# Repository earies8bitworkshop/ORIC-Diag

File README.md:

# ORIC-Diag
This is a convertion of the ORIC Diagnostic PCB located at https://oric.signal11.org.uk/html/diagrom.htm Unfortunately with EAGLE going end of life it was tough going to get the PCB orders. This is a KICAD conversion of the original, no changes made as of 7/9/25. The Gerbers are located in production/OricDiagBoard.zip and can be uploaded directly to your favourite PCB manufacturer. 

NOTE: Mike Brown is the original author of the works, I take no credit for it this is a direct conversion into Kicad only.

NOTE: The kicad coversion needs some clean up it misidentified the diodes as Pots. If you make changes to the board feel free to tidy up the autoconversion but what we have is good enough to generate the gerbers for manufacture.

# Oric Repair Checklist
Again, just a conversion. This time adding the PCB images into the word doc rather than being in a separate ZIP file. All credits go to the Author MJB. Also corrected the text with the errata noted on the source web site. https://oric.signal11.org.uk/html/repairguide.htm

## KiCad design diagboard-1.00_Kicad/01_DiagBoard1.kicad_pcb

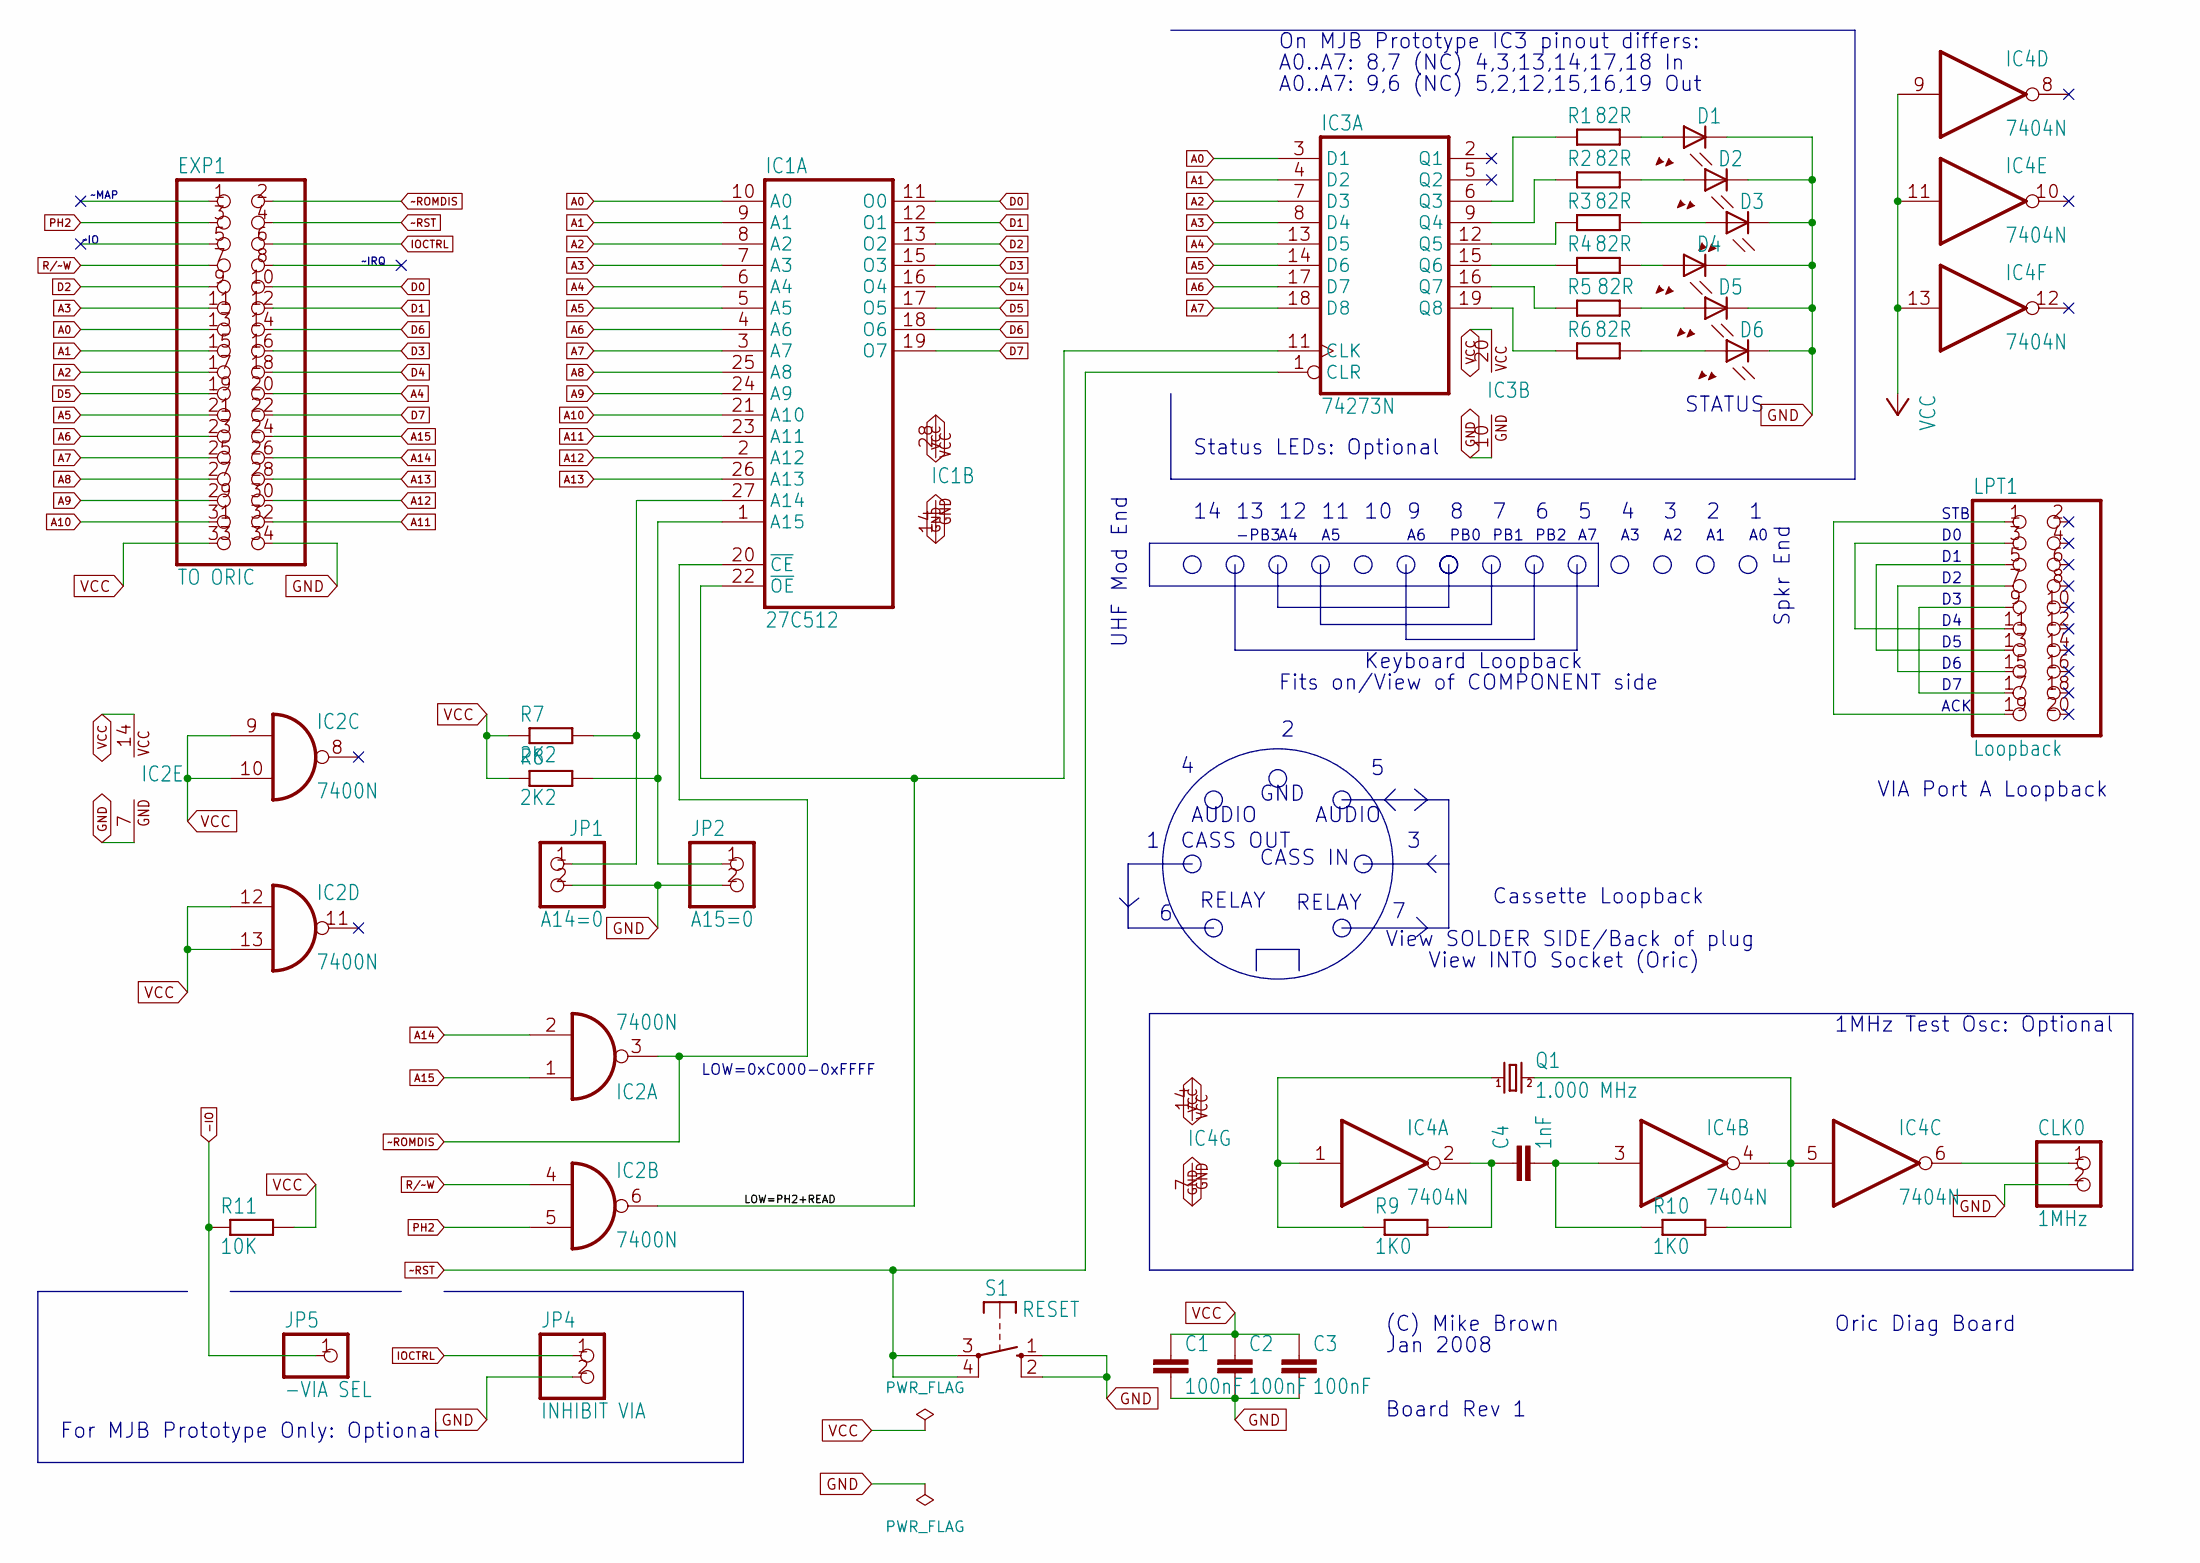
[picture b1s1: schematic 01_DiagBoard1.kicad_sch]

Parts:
C1, C2, C3: 100nF; C050-024X044
C4: 1nF; C050-024X044
CLK0: 1MHz; 1X02
D1, D2, D3, D4, D5, D6: U57X32
EXP1: TO ORIC; 2X17
IC1: 27C512; DIL28
IC2: 7400N; DIL14
IC3: 74273N; DIL20
IC4: 7404N; DIL14
JP1: A14=0; 1X02
JP2: A15=0; 1X02
JP4: INHIBIT VIA; 1X02
JP5: -VIA SEL; 1X01
LPT1: Loopback; 2X10
Q1: 1.000 MHz; HC18U-V
R1, R2, R3, R4, R5, R6: 82R; 0204V
R7, R8: 2K2; 0204V
R9, R10: 1K0; 0204V
R11: 10K; 0204V
S1: RESET; DT6

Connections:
-IO: JP5.1, R11.1
/LOW=PH2+READ: IC1.22 (~OE), IC2.6 (O), IC3.11 (CLK)
A0: EXP1.13, IC1.10 (A0), IC3.3 (D1)
A1: EXP1.15, IC1.9 (A1), IC3.4 (D2)
A2: EXP1.17, IC1.8 (A2), IC3.7 (D3)
A3: EXP1.11, IC1.7 (A3), IC3.8 (D4)
A4: EXP1.20, IC1.6 (A4), IC3.13 (D5)
A5: EXP1.21, IC1.5 (A5), IC3.14 (D6)
A6: EXP1.23, IC1.4 (A6), IC3.17 (D7)
A7: EXP1.25, IC1.3 (A7), IC3.18 (D8)
A8: EXP1.27, IC1.25 (A8)
A9: EXP1.29, IC1.24 (A9)
A10: EXP1.31, IC1.21 (A10)
A11: EXP1.32, IC1.23 (A11)
A12: EXP1.30, IC1.2 (A12)
A13: EXP1.28, IC1.26 (A13)
A14: EXP1.26, IC2.2 (I1)
A15: EXP1.24, IC2.1 (I0)
D0: EXP1.10, IC1.11 (O0)
D1: EXP1.12, IC1.12 (O1)
D2: EXP1.9, IC1.13 (O2)
D3: EXP1.16, IC1.15 (O3)
D4: EXP1.18, IC1.16 (O4)
D5: EXP1.19, IC1.17 (O5)
D6: EXP1.14, IC1.18 (O6)
D7: EXP1.22, IC1.19 (O7)
GND: C1.2, C2.2, C3.2, CLK0.2, D1.K (C), D2.K (C), D3.K (C), D4.K (C), D5.K (C), D6.K (C), EXP1.34, IC1.14 (GND), IC2.7 (GND), IC3.10 (GND), IC4.7 (GND), JP1.2, JP2.2, JP4.2, S1.1 (S), S1.2 (S@1)
IOCTRL: EXP1.6, JP4.1
unnamed: D1.A, R1.2
unnamed: D2.A, R2.2
unnamed: D3.A, R3.2
unnamed: D4.A, R4.2
unnamed: D5.A, R5.2
unnamed: D6.A, R6.2
unnamed: IC1.27 (A14), JP1.1, R7.2
unnamed: IC1.1 (A15), JP2.1, R8.2
unnamed: IC3.6 (Q3), R1.1
unnamed: IC3.9 (Q4), R2.1
unnamed: IC3.12 (Q5), R3.1
unnamed: IC3.15 (Q6), R4.1
unnamed: IC3.16 (Q7), R5.1
unnamed: IC3.19 (Q8), R6.1
unnamed: IC4.1 (I), Q1.1, R9.1
unnamed: C4.1, IC4.2 (O), R9.2
unnamed: C4.2, IC4.3 (I), R10.1
unnamed: IC4.4 (O), IC4.5 (I), Q1.2, R10.2
unnamed: CLK0.1, IC4.6 (O)
unnamed: LPT1.1, LPT1.19
unnamed: LPT1.3, LPT1.11
unnamed: LPT1.5, LPT1.13
unnamed: LPT1.7, LPT1.15
unnamed: LPT1.9, LPT1.17
PH2: EXP1.3, IC2.5 (I1)
R/~W: EXP1.7, IC2.4 (I0)
VCC: C1.1, C2.1, C3.1, EXP1.33, IC1.28 (VCC), IC2.9 (I0), IC2.10 (I1), IC2.12 (I0), IC2.13 (I1), IC2.14 (VCC), IC3.20 (VCC), IC4.9 (I), IC4.11 (I), IC4.13 (I), IC4.14 (VCC), R7.1, R8.1, R11.2
~ROMDIS: EXP1.2, IC1.20 (~CE), IC2.3 (O)
~RST: EXP1.4, IC3.1 (CLR), S1.3, S1.4 (P@1)

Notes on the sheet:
~IRQ
Status LEDs: Optional
AUDIO
UHF Mod End
On MJB Prototype IC3 pinout differs:
~IO
PB1
ACK
PB2
1MHz Test Osc: Optional
CASS OUT
STB
Spkr End
Oric Diag Board
Cassette Loopback
Board Rev 1
For MJB Prototype Only: Optional
-PB3
~MAP
PB0
Fits on/View of COMPONENT side
Jan 2008
A0..A7: 8,7 (NC) 4,3,13,14,17,18 In
RELAY
VIA Port A Loopback
A0..A7: 9,6 (NC) 5,2,12,15,16,19 Out
Keyboard Loopback
View INTO Socket (Oric)
CASS IN
GND
View SOLDER SIDE/Back of plug
LOW=0xC000-0xFFFF
(C) Mike Brown
STATUS

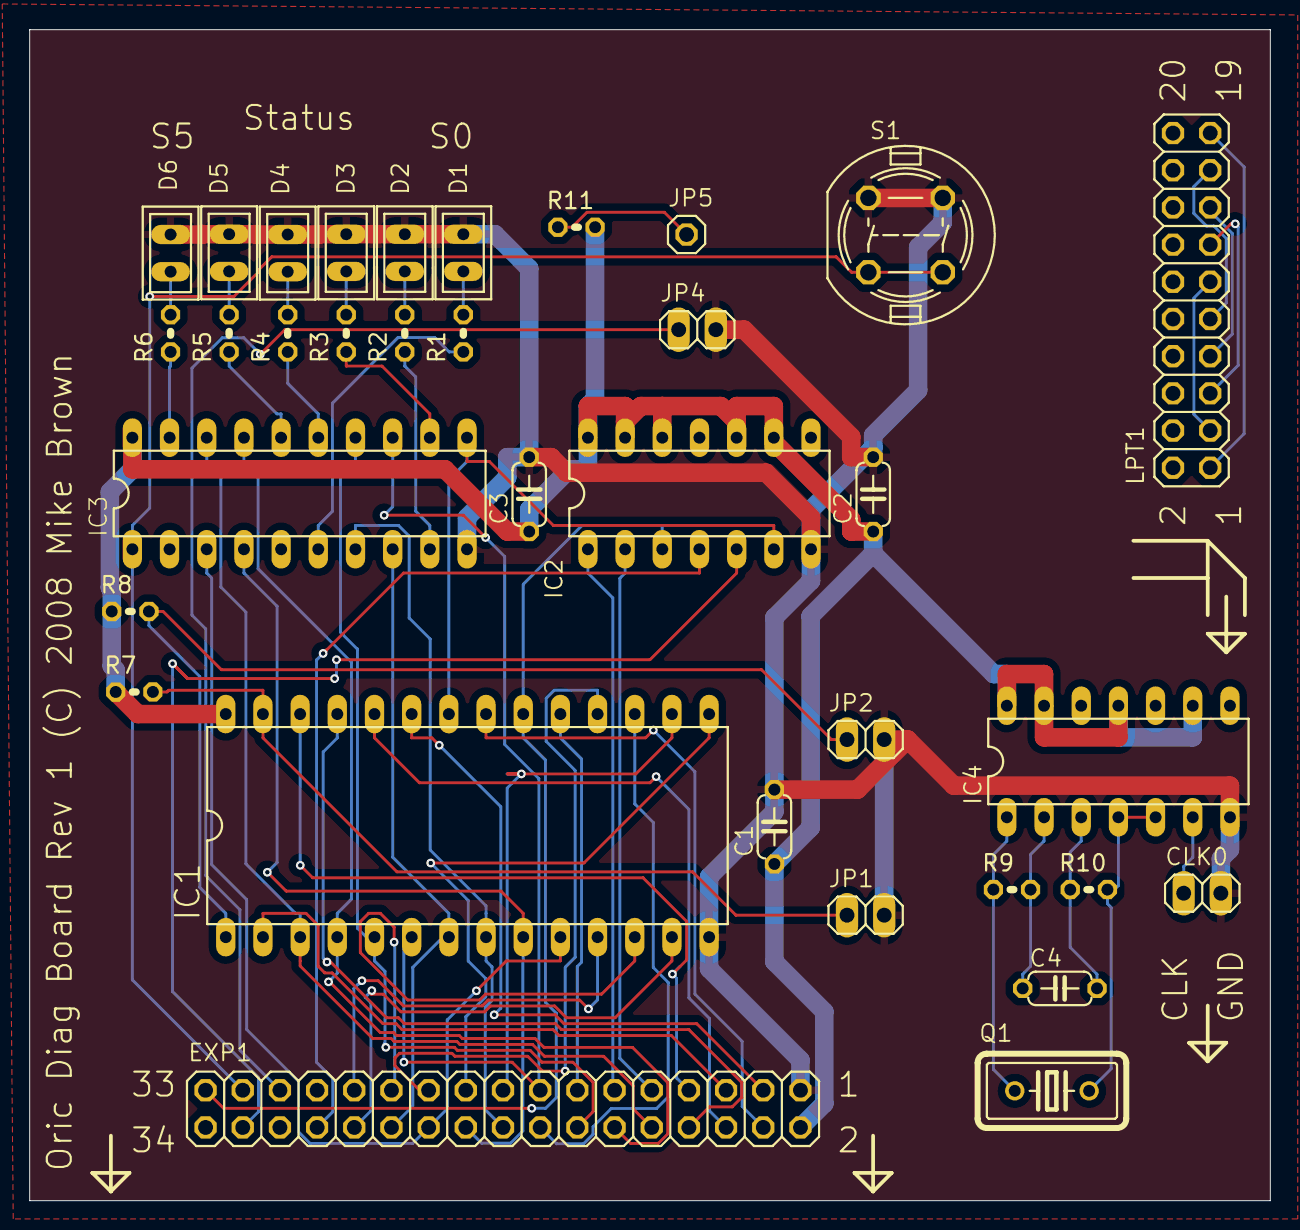
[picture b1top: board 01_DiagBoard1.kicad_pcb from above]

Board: 2 copper layers, 84.8 x 80.0 mm, 34 parts (0 on the bottom side), 57 nets.

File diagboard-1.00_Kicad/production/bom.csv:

Designator,Footprint,Quantity,Value,LCSC Part #
"C1, C2, C3",C050-024X044,3,100nF,
C4,C050-024X044,1,1nF,
CLK0,1X02,1,1MHz,
"D1, D2, D3, D4, D5, D6",U57X32,6,U57X32,
EXP1,2X17,1,TO ORIC,
IC1,DIL28,1,27C512,
IC2,DIL14,1,7400N,
IC3,DIL20,1,74273N,
IC4,DIL14,1,7404N,
JP1,1X02,1,A14=0,
JP2,1X02,1,A15=0,
JP4,1X02,1,INHIBIT VIA,
JP5,1X01,1,-VIA SEL,
LPT1,2X10,1,Loopback,
Q1,HC18U-V,1,1.000 MHz,
"R1, R2, R3, R4, R5",0204V,5,82R,
"R10, R9",0204V,2,1K0,
R11,0204V,1,10K,
R6,0204V,1,6 x 82R,
"R7, R8",0204V,2,2K2,
S1,DT6,1,RESET,

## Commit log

2025-10-30 deleted: diagboard-1.00_Kicad/production/OricDiagBoard.zip

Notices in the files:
diagboard-1.00_Kicad/01_DiagBoard1.kicad_pcb:
Oric Diag Board Rev 1 (C) 2008 Mike Brown
